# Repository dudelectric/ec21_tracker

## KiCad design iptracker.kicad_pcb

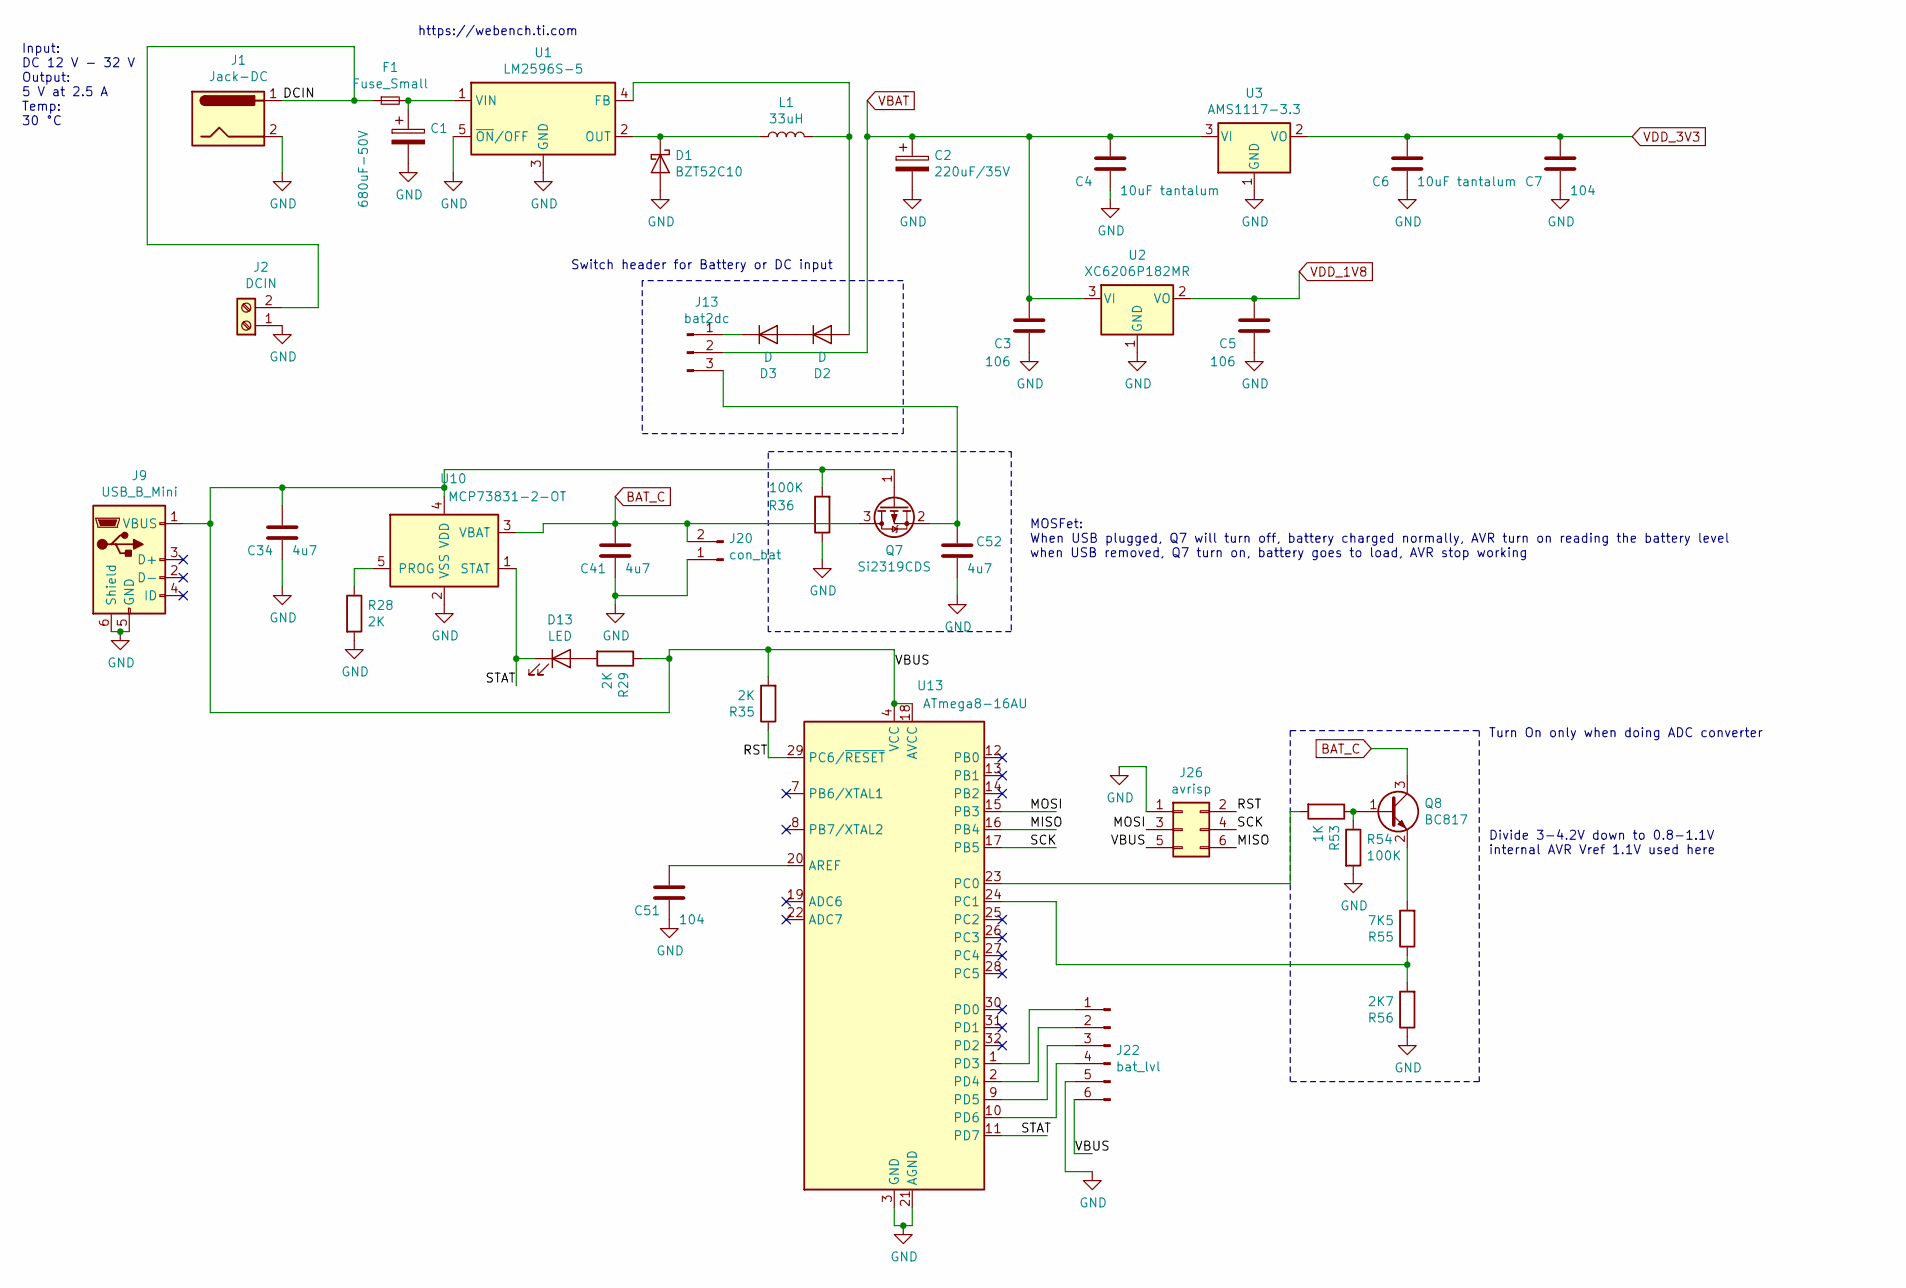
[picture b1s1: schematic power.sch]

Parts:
C1: 680uF-50V; CP_Elec_10x10
C2: 220uF/35V; CP_Elec_10x10
C3, C5: 106; C_0805_2012Metric_Pad1.15x1.40mm_HandSolder
C4, C6: 10uF tantalum; C_1210_3225Metric_Pad1.42x2.65mm_HandSolder
C7, C51: 104; C_0805_2012Metric_Pad1.15x1.40mm_HandSolder
C34, C41, C52: 4u7; C_0805_2012Metric_Pad1.15x1.40mm_HandSolder
D1: BZT52C10; D_SMA_Handsoldering
D2, D3: D; D_SMA_Handsoldering
D13: LED; LED_0805_2012Metric_Pad1.15x1.40mm_HandSolder
F1: Fuse_Small; Fuse_1806_4516Metric
J1: Jack-DC; BarrelJack_Horizontal
J2: DCIN; TerminalBlock_bornier-2_P5.08mm
J9: USB_B_Mini; USB_Mini-B_Lumberg_2486_01_Horizontal
J13: bat2dc; PinHeader_1x03_P2.54mm_Vertical
J20: con_bat; JST_PH_B2B-PH-K_1x02_P2.00mm_Vertical
J22: bat_lvl; PinHeader_1x06_P2.54mm_Vertical
J26: avrisp; PinHeader_2x03_P2.54mm_Vertical
L1: 33uH; L_Neosid_SM-NE127_HandSoldering
Q7: Si2319CDS; SOT-23
Q8: BC817; SOT-23
R28, R29, R35: 2K; R_0805_2012Metric_Pad1.15x1.40mm_HandSolder
R36, R54: 100K; R_0805_2012Metric_Pad1.15x1.40mm_HandSolder
R53: 1K; R_0805_2012Metric_Pad1.15x1.40mm_HandSolder
R55: 7K5; R_0805_2012Metric_Pad1.15x1.40mm_HandSolder
R56: 2K7; R_0805_2012Metric_Pad1.15x1.40mm_HandSolder
U1: LM2596S-5; TO-263-5_TabPin3
U2: XC6206P182MR; SOT-23
U3: AMS1117-3.3; SOT-223-3_TabPin2
U10: MCP73831-2-OT; SOT-23-5
U13: ATmega8-16AU; TQFP-32_7x7mm_P0.8mm

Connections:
/power/DCIN: F1.1, J1.1, J2.2
/power/MISO: J26.6, U13.16 (PB4)
/power/MOSI: J26.3, U13.15 (PB3)
/power/RST: J26.2, R35.1, U13.29 (PC6/~RESET)
/power/SCK: J26.4, U13.17 (PB5)
/power/STAT: D13.1 (K), U10.1 (STAT), U13.11 (PD7)
/power/VBUS: C34.1, J9.1 (VBUS), J22.6, J26.5, Q7.1 (G), R29.1, R35.2, R36.2, U10.4 (VDD), U13.4 (VCC), U13.6 (VCC), U13.18 (AVCC)
BAT_C: C41.1, J20.2, Q7.3 (D), Q8.3 (C), U10.3 (VBAT); also elsewhere on the board
GND: C1.2, C2.2, C3.2, C4.2, C5.2, C6.2, C7.2, C34.2, C41.2, C51.2, C52.2, D1.2 (A), J1.2, J2.1, J9.5 (GND), J9.6 (Shield), J20.1, J22.5, J26.1, R28.2, R36.1, R54.2, R56.1, U1.3 (GND), U1.5 (~ON~/OFF), U2.1 (GND), U3.1 (GND), U10.2 (VSS), U13.3 (GND), U13.5 (GND), U13.21 (AGND); also elsewhere on the board
unnamed: C1.1, F1.2, U1.1 (VIN)
unnamed: C51.1, U13.20 (AREF)
unnamed: C52.1, J13.3, Q7.2 (S)
unnamed: D1.1 (K), L1.1, U1.2 (OUT)
unnamed: D2.1 (K), D3.2 (A)
unnamed: D2.2 (A), L1.2, U1.4 (FB)
unnamed: D3.1 (K), J13.1
unnamed: D13.2 (A), R29.2
unnamed: J22.1, U13.1 (PD3)
unnamed: J22.2, U13.2 (PD4)
unnamed: J22.3, U13.9 (PD5)
unnamed: J22.4, U13.10 (PD6)
unnamed: Q8.1 (B), R53.1, R54.1
unnamed: Q8.2 (E), R55.2
unnamed: R28.1, U10.5 (PROG)
unnamed: R53.2, U13.23 (PC0)
unnamed: R55.1, R56.2, U13.24 (PC1)
VBAT: C2.1, C3.1, C4.1, J13.2, U2.3 (VI), U3.3 (VI); also elsewhere on the board
VDD_1V8: C5.1, U2.2 (VO)
VDD_3V3: C6.1, C7.1, U3.2 (VO); also elsewhere on the board

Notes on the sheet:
Input: DC 12 V - 32 V Output: 5 V at 2.5 A Temp: 30 °C
https://webench.ti.com
Switch header for Battery or DC input
Turn On only when doing ADC converter
Divide 3-4.2V down to 0.8-1.1V internal AVR Vref 1.1V used here
MOSFet: When USB plugged, Q7 will turn off, battery charged normally, AVR turn on reading the battery level when USB removed, Q7 turn on, battery goes to load, AVR stop working

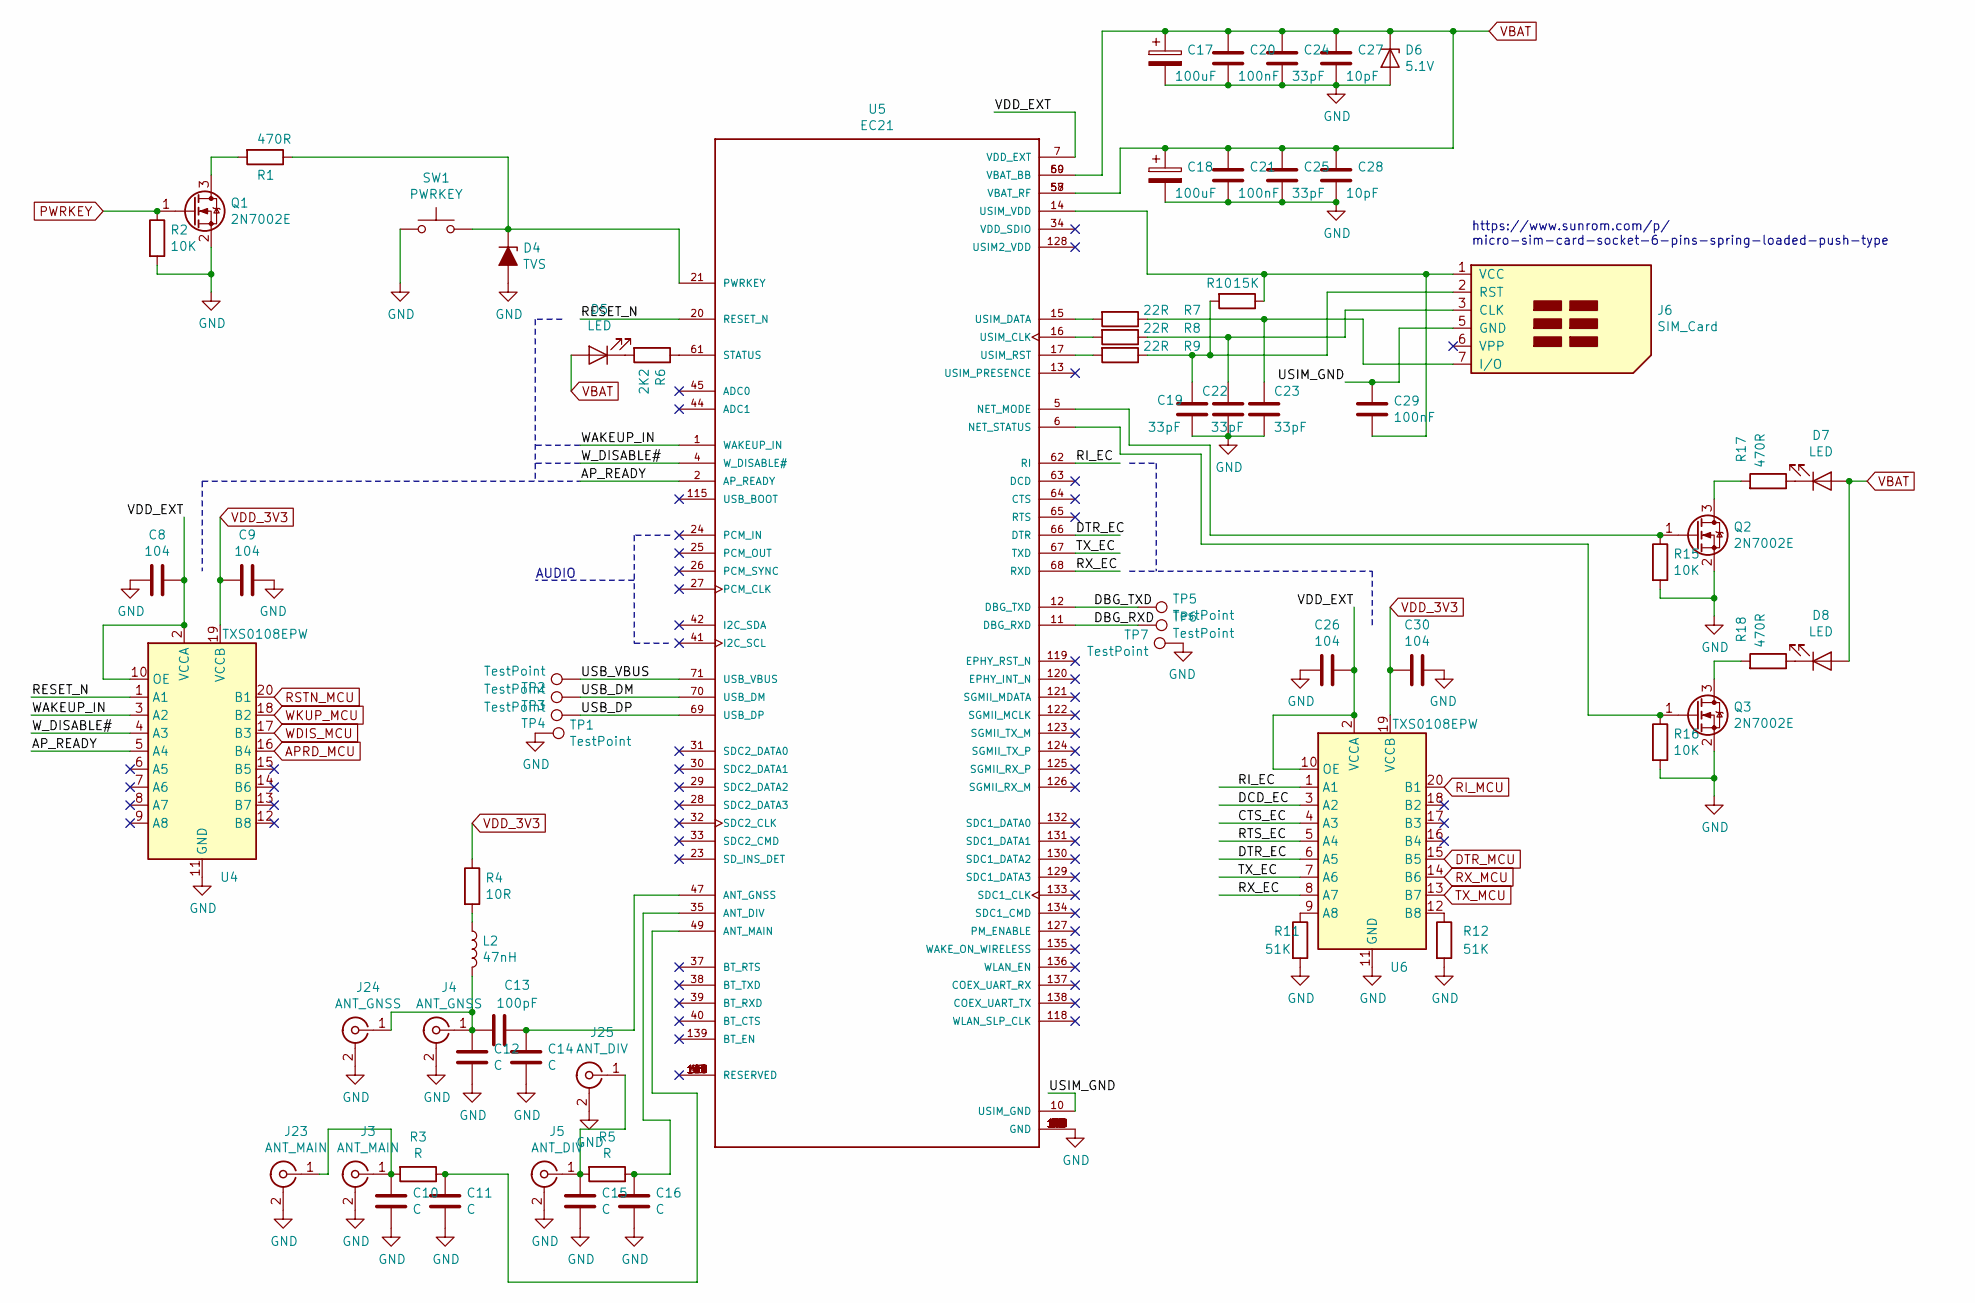
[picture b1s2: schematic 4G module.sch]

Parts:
C8, C9, C26, C30: 104; C_0805_2012Metric_Pad1.15x1.40mm_HandSolder
C10, C11, C12, C14, C15, C16: C; C_0805_2012Metric_Pad1.15x1.40mm_HandSolder
C13: 100pF; C_0805_2012Metric_Pad1.15x1.40mm_HandSolder
C17, C18: 100uF; CP_Elec_6.3x5.4
C19, C22, C23, C24, C25: 33pF; C_0805_2012Metric_Pad1.15x1.40mm_HandSolder
C20, C21, C29: 100nF; C_0805_2012Metric_Pad1.15x1.40mm_HandSolder
C27, C28: 10pF; C_0805_2012Metric_Pad1.15x1.40mm_HandSolder
D4: TVS; D_SMA_Handsoldering
D5, D7, D8: LED; LED_0805_2012Metric_Pad1.15x1.40mm_HandSolder
D6: 5.1V; D_SMA_Handsoldering
J3: ANT_MAIN; U.FL_Hirose_U.FL-R-SMT-1_Vertical
J4: ANT_GNSS; U.FL_Hirose_U.FL-R-SMT-1_Vertical
J5: ANT_DIV; U.FL_Hirose_U.FL-R-SMT-1_Vertical
J6: SIM_Card; Micro SIM Card Socket - 6 pins - Spring Loaded Push type
J23: ANT_MAIN; SMA_Molex_73251-2200_Horizontal
J24: ANT_GNSS; SMA_Molex_73251-2200_Horizontal
J25: ANT_DIV; SMA_Molex_73251-2200_Horizontal
L2: 47nH; L_0805_2012Metric_Pad1.15x1.40mm_HandSolder
Q1, Q2, Q3: 2N7002E; SOT-23
R1, R17, R18: 470R; R_0805_2012Metric_Pad1.15x1.40mm_HandSolder
R2, R15, R16: 10K; R_0805_2012Metric_Pad1.15x1.40mm_HandSolder
R3, R5: R; R_0805_2012Metric_Pad1.15x1.40mm_HandSolder
R4: 10R; R_0805_2012Metric_Pad1.15x1.40mm_HandSolder
R6: 2K2; R_0805_2012Metric_Pad1.15x1.40mm_HandSolder
R7, R8, R9: 22R; R_0805_2012Metric_Pad1.15x1.40mm_HandSolder
R10: 15K; R_0805_2012Metric_Pad1.15x1.40mm_HandSolder
R11, R12: 51K; R_0805_2012Metric_Pad1.15x1.40mm_HandSolder
SW1: PWRKEY; SW_PUSH_6mm
TP1, TP2, TP3, TP4, TP5, TP6, TP7: TestPoint; TestPoint_Pad_1.5x1.5mm
U4, U6: TXS0108EPW; TSSOP-20_4.4x6.5mm_P0.65mm
U5: EC21; XDCR_EC21

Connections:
/4G module/AP_READY: U4.5 (A4), U5.2 (AP_READY)
/4G module/DBG_RXD: TP6.1, U5.11 (DBG_RXD)
/4G module/DBG_TXD: TP5.1, U5.12 (DBG_TXD)
/4G module/DTR_EC: U5.66 (DTR), U6.6 (A5)
/4G module/RESET_N: U4.1 (A1), U5.20 (RESET_N)
/4G module/RI_EC: U5.62 (RI), U6.1 (A1)
/4G module/RX_EC: U5.68 (RXD), U6.8 (A7)
/4G module/TX_EC: U5.67 (TXD), U6.7 (A6)
/4G module/USB_DM: TP3.1, U5.70 (USB_DM)
/4G module/USB_DP: TP4.1, U5.69 (USB_DP)
/4G module/USB_VBUS: TP2.1, U5.71 (USB_VBUS)
/4G module/USIM_GND: C29.1, J6.5 (GND), U5.10 (USIM_GND)
/4G module/VDD_EXT: C8.1, C26.1, U4.2 (VCCA), U4.10 (OE), U5.7 (VDD_EXT), U6.2 (VCCA), U6.10 (OE)
/4G module/WAKEUP_IN: U4.3 (A2), U5.1 (WAKEUP_IN)
/4G module/W_DISABLE#: U4.4 (A3), U5.4 (W_DISABLE#)
APRD_MCU: U4.16 (B4); also elsewhere on the board
DTR_MCU: U6.15 (B5); also elsewhere on the board
GND: C8.2, C9.2, C10.2, C11.2, C12.2, C14.2, C15.2, C16.2, C17.2, C18.2, C19.2, C20.2, C21.2, C22.2, C23.2, C24.2, C25.2, C26.2, C27.2, C28.2, C30.2, D4.2 (A), D6.2 (A), J3.2 (Ext), J4.2 (Ext), J5.2 (Ext), J23.2 (Ext), J24.2 (Ext), J25.2 (Ext), Q1.2 (S), Q2.2 (S), Q3.2 (S), R2.2, R11.2, R12.2, R15.2, R16.2, SW1.1, TP1.1, TP7.1, U4.11 (GND), U5.8 (GND), U5.9 (GND), U5.19 (GND), U5.22 (GND), U5.36 (GND), U5.46 (GND), U5.48 (GND), U5.50 (GND), U5.51 (GND), U5.52 (GND), U5.53 (GND), U5.54 (GND), U5.56 (GND), U5.72 (GND), U5.85 (GND), U5.86 (GND), U5.87 (GND), U5.88 (GND), U5.89 (GND), U5.90 (GND), U5.91 (GND), U5.92 (GND), U5.93 (GND), U5.94 (GND), U5.95 (GND), U5.96 (GND), U5.97 (GND), U5.98 (GND), U5.99 (GND), U5.100 (GND), U5.101 (GND), U5.102 (GND), U5.103 (GND), U5.104 (GND), U5.105 (GND), U5.106 (GND), U5.107 (GND), U5.108 (GND), U5.109 (GND), U5.110 (GND), U5.111 (GND), U5.112 (GND), U6.11 (GND); also elsewhere on the board
unnamed: C10.1, J3.1 (In), J23.1 (In), R3.2
unnamed: C11.1, R3.1, U5.49 (ANT_MAIN)
unnamed: C12.1, C13.2, J4.1 (In), J24.1 (In), L2.2
unnamed: C13.1, C14.1, U5.47 (ANT_GNSS)
unnamed: C15.1, J5.1 (In), J25.1 (In), R5.2
unnamed: C16.1, R5.1, U5.35 (ANT_DIV)
unnamed: C19.1, J6.2 (RST), R9.1, R10.2
unnamed: C22.1, J6.3 (CLK), R8.1
unnamed: C23.1, J6.7 (I/O), R7.1
unnamed: C29.2, J6.1 (VCC), R10.1, U5.14 (USIM_VDD)
unnamed: D4.1 (K), R1.1, SW1.2, U5.21 (PWRKEY)
unnamed: D5.1 (K), R6.2
unnamed: D7.1 (K), R17.1
unnamed: D8.1 (K), R18.1
unnamed: L2.1, R4.2
unnamed: Q1.3 (D), R1.2
unnamed: Q2.1 (G), R15.1, U5.5 (NET_MODE)
unnamed: Q2.3 (D), R17.2
unnamed: Q3.1 (G), R16.1, U5.6 (NET_STATUS)
unnamed: Q3.3 (D), R18.2
unnamed: R6.1, U5.61 (STATUS)
unnamed: R7.2, U5.15 (USIM_DATA)
unnamed: R8.2, U5.16 (USIM_CLK)
unnamed: R9.2, U5.17 (USIM_RST)
unnamed: R11.1, U6.9 (A8)
unnamed: R12.1, U6.12 (B8)
unnamed: U5.3 (RESERVED), U5.18 (RESERVED), U5.43 (RESERVED), U5.55 (RESERVED), U5.113 (RESERVED), U5.114 (RESERVED), U5.116 (RESERVED), U5.117 (RESERVED), U5.140 (RESERVED), U5.141 (RESERVED), U5.142 (RESERVED), U5.143 (RESERVED), U5.144 (RESERVED)
PWRKEY: Q1.1 (G), R2.1
RI_MCU: U6.20 (B1); also elsewhere on the board
RSTN_MCU: U4.20 (B1); also elsewhere on the board
RX_MCU: U6.14 (B6); also elsewhere on the board
TX_MCU: U6.13 (B7); also elsewhere on the board
VBAT: C17.1, C18.1, C20.1, C21.1, C24.1, C25.1, C27.1, C28.1, D5.2 (A), D6.1 (K), D7.2 (A), D8.2 (A), U5.57 (VBAT_RF), U5.58 (VBAT_RF), U5.59 (VBAT_BB), U5.60 (VBAT_BB); also elsewhere on the board
VDD_3V3: C9.1, C30.1, R4.1, U4.19 (VCCB), U6.19 (VCCB); also elsewhere on the board
WDIS_MCU: U4.17 (B3); also elsewhere on the board
WKUP_MCU: U4.18 (B2); also elsewhere on the board

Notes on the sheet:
AUDIO
https://www.sunrom.com/p/ micro-sim-card-socket-6-pins-spring-loaded-push-type

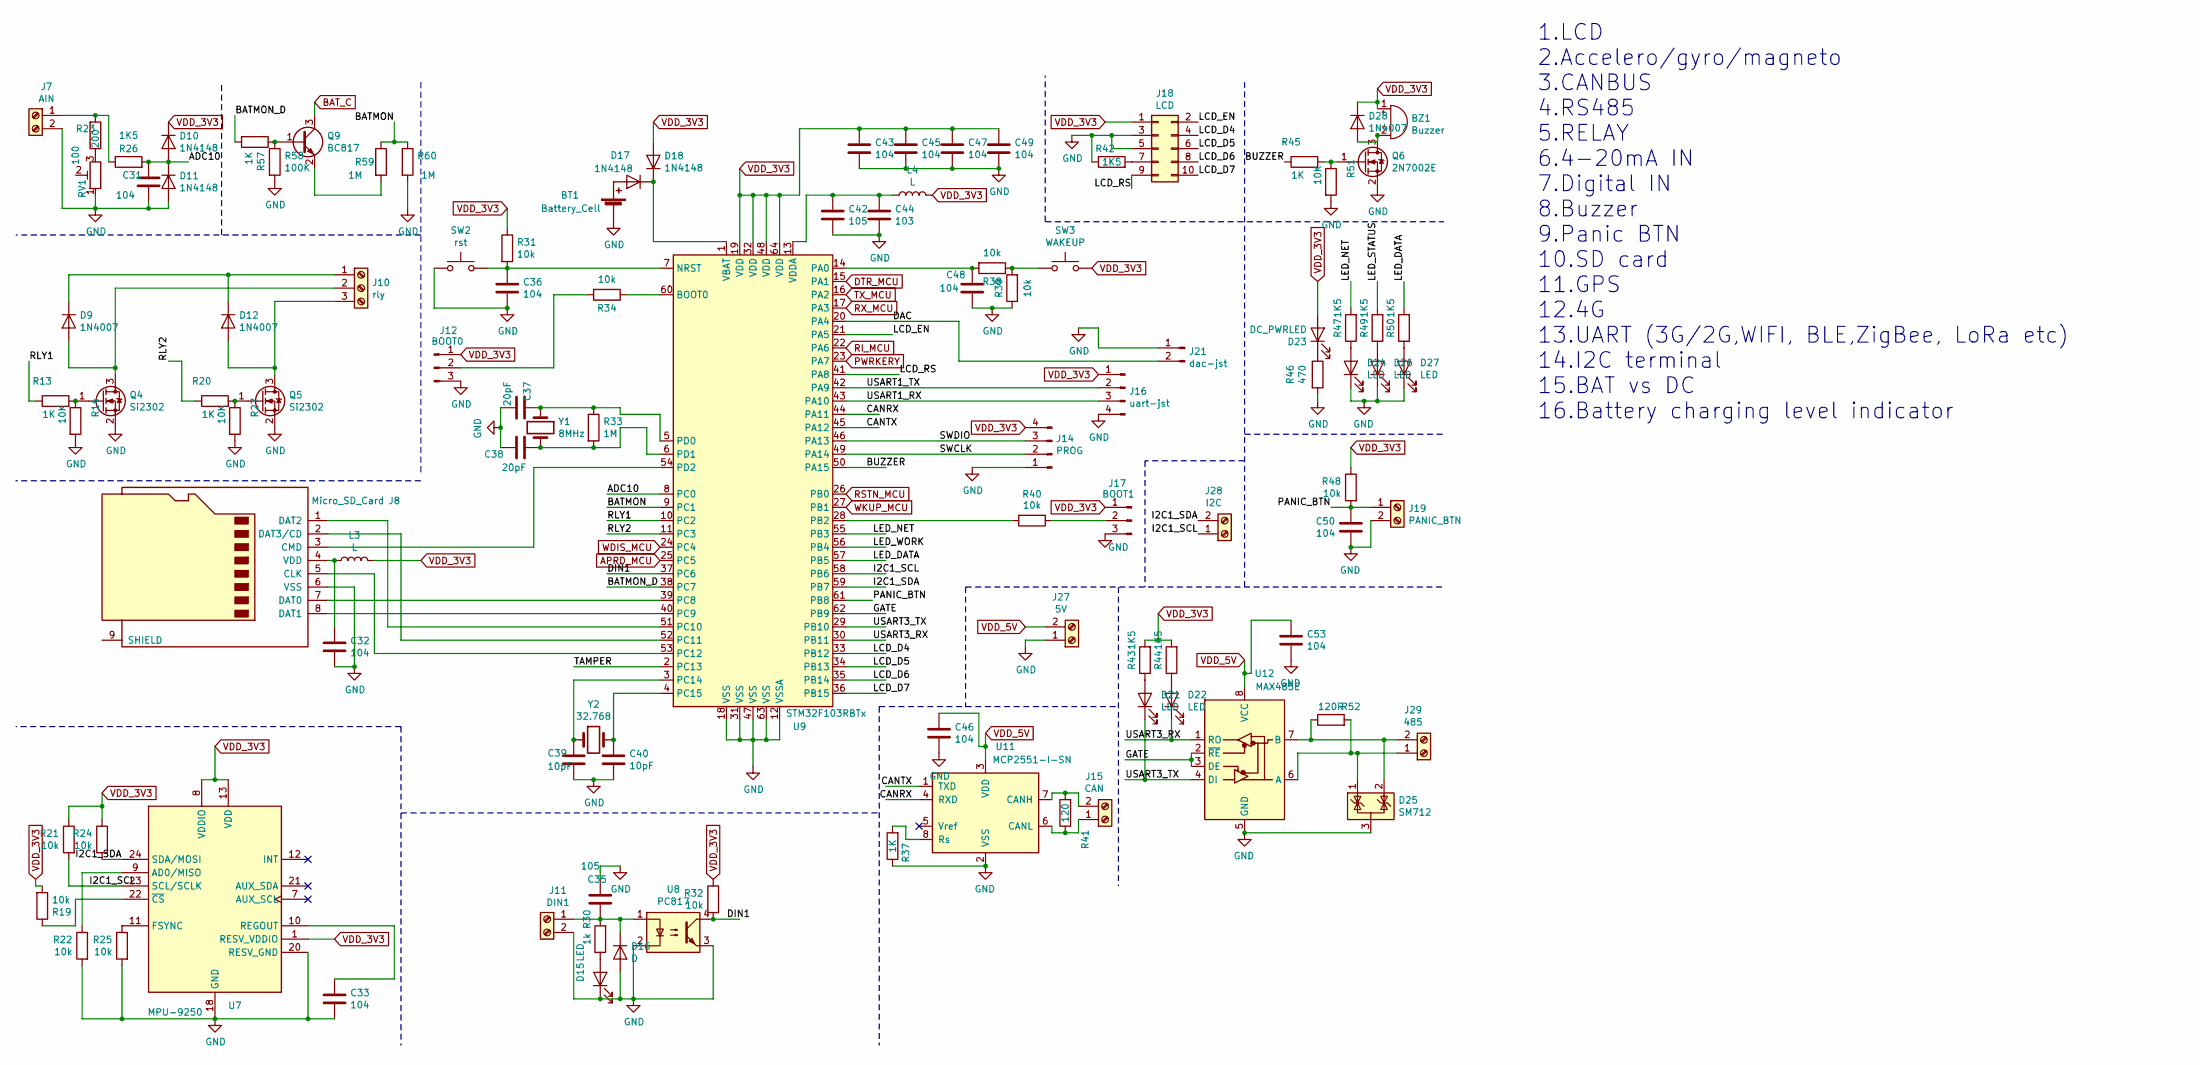
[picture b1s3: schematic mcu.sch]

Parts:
BT1: Battery_Cell; BatteryHolder_Keystone_3001_1x12mm
BZ1: Buzzer; Buzzer_12x9.5RM7.6
C31, C32, C33, C36, C43, C45, C46, C47, C48, C49, C50, C53: 104; C_0805_2012Metric_Pad1.15x1.40mm_HandSolder
C35, C42: 105; C_0805_2012Metric_Pad1.15x1.40mm_HandSolder
C37, C38: 20pF; C_0805_2012Metric_Pad1.15x1.40mm_HandSolder
C39, C40: 10pF; C_0805_2012Metric_Pad1.15x1.40mm_HandSolder
C44: 103; C_0805_2012Metric_Pad1.15x1.40mm_HandSolder
D9, D12, D28: 1N4007; D_SMA_Handsoldering
D10, D11, D17, D18: 1N4148; D_MELF
D15, D21, D22, D24, D26, D27: LED; LED_0805_2012Metric_Pad1.15x1.40mm_HandSolder
D16: D; D_MELF
D23: DC_PWRLED; LED_0805_2012Metric_Pad1.15x1.40mm_HandSolder
D25: SM712; SOT-23
J7: AIN; TerminalBlock_bornier-2_P5.08mm
J8: Micro_SD_Card; GCT-MEM2055-00-190-01-A
J10: rly; TerminalBlock_bornier-3_P5.08mm
J11: DIN1; TerminalBlock_bornier-2_P5.08mm
J12: BOOT0; PinHeader_1x03_P2.54mm_Vertical
J14: PROG; PinHeader_1x04_P2.54mm_Vertical
J15: CAN; TerminalBlock_bornier-2_P5.08mm
J16: uart-jst; JST_PH_B4B-PH-K_1x04_P2.00mm_Vertical
J17: BOOT1; PinHeader_1x03_P2.54mm_Vertical
J18: LCD; JST_PHD_B10B-PHDSS_2x05_P2.00mm_Vertical
J19: PANIC_BTN; TerminalBlock_bornier-2_P5.08mm
J21: dac-jst; JST_PH_B2B-PH-K_1x02_P2.00mm_Vertical
J27: 5V; TerminalBlock_bornier-2_P5.08mm
J28: I2C; TerminalBlock_bornier-2_P5.08mm
J29: 485; TerminalBlock_bornier-2_P5.08mm
L3, L4: L; L_0805_2012Metric_Pad1.15x1.40mm_HandSolder
Q4, Q5: Si2302; SOT-23
Q6: 2N7002E; SOT-23
Q9: BC817; SOT-23
R13, R20, R37, R45, R57: 1K; R_0805_2012Metric_Pad1.15x1.40mm_HandSolder
R14, R27, R51: 10K; R_0805_2012Metric_Pad1.15x1.40mm_HandSolder
R19, R21, R22, R24, R25, R31, R32, R34, R38, R39, R40, R48: 10k; R_0805_2012Metric_Pad1.15x1.40mm_HandSolder
R23: 200; R_0805_2012Metric_Pad1.15x1.40mm_HandSolder
R26, R42, R43, R44, R47, R49, R50: 1K5; R_0805_2012Metric_Pad1.15x1.40mm_HandSolder
R30: 1k; R_0805_2012Metric_Pad1.15x1.40mm_HandSolder
R33, R59, R60: 1M; R_0805_2012Metric_Pad1.15x1.40mm_HandSolder
R41: 120; R_0805_2012Metric_Pad1.15x1.40mm_HandSolder
R46: 470; R_0805_2012Metric_Pad1.15x1.40mm_HandSolder
R52: 120R; R_0805_2012Metric_Pad1.15x1.40mm_HandSolder
R58: 100K; R_0805_2012Metric_Pad1.15x1.40mm_HandSolder
RV1: 100; Potentiometer_Vishay_TS53YL_Vertical
SW2: rst; SW_PUSH_6mm
SW3: WAKEUP; SW_PUSH_6mm
U7: MPU-9250; InvenSense_QFN-24_3x3mm_P0.4mm
U8: PC817; DIP-4_W7.62mm
U9: STM32F103RBTx; LQFP-64_10x10mm_P0.5mm
U11: MCP2551-I-SN; SOIC-8_3.9x4.9mm_P1.27mm
U12: MAX485E; SOIC-8_3.9x4.9mm_P1.27mm
Y1: 8MHz; Crystal_HC49-4H_Vertical
Y2: 32.768; Crystal_SMD_SeikoEpson_MA406-4Pin_11.7x4.0mm_HandSoldering

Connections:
/mcu/ADC10: C31.1, D10.2 (A), D11.1 (K), R26.2, U9.8 (PC0)
/mcu/BATMON: R59.1, R60.1, U9.9 (PC1)
/mcu/BATMON_D: R57.2, U9.38 (PC7)
/mcu/BUZZER: R45.1, U9.50 (PA15)
/mcu/CANRX: U9.44 (PA11), U11.4 (RXD)
/mcu/CANTX: U9.45 (PA12), U11.1 (TXD)
/mcu/DAC: J21.2, U9.20 (PA4)
/mcu/DIN1: R32.2, U8.4, U9.37 (PC6)
/mcu/GATE: U9.62 (PB9), U12.2 (~RE), U12.3 (DE)
/mcu/I2C1_SCL: J28.1, R21.2, U7.23 (SCL/SCLK), U9.58 (PB6)
/mcu/I2C1_SDA: J28.2, R24.2, U7.24 (SDA/MOSI), U9.59 (PB7)
/mcu/LCD_D4: J18.4, U9.33 (PB12)
/mcu/LCD_D5: J18.6, U9.34 (PB13)
/mcu/LCD_D6: J18.8, U9.35 (PB14)
/mcu/LCD_D7: J18.10, U9.36 (PB15)
/mcu/LCD_EN: J18.2, U9.21 (PA5)
/mcu/LCD_RS: J18.9, U9.41 (PA8)
/mcu/LED_DATA: R50.2, U9.57 (PB5)
/mcu/LED_NET: R47.2, U9.55 (PB3)
/mcu/PANIC_BTN: C50.1, J19.1, R48.2, U9.61 (PB8)
/mcu/RLY1: R13.1, U9.10 (PC2)
/mcu/RLY2: R20.1, U9.11 (PC3)
/mcu/SWCLK: J14.2, U9.49 (PA14)
/mcu/SWDIO: J14.3, U9.46 (PA13)
/mcu/USART1_RX: J16.3, U9.43 (PA10)
/mcu/USART1_TX: J16.2, U9.42 (PA9)
/mcu/USART3_RX: D22.1 (K), U9.30 (PB11), U12.1 (RO)
/mcu/USART3_TX: D21.1 (K), U9.29 (PB10), U12.4 (DI)
APRD_MCU: U9.25 (PC5); also elsewhere on the board
BAT_C: Q9.3 (C); also elsewhere on the board
DTR_MCU: U9.15 (PA1); also elsewhere on the board
GND: BT1.2 (-), C31.2, C32.2, C33.2, C35.1, C36.2, C37.1, C38.2, C39.1, C40.2, C42.2, C43.2, C44.2, C45.2, C46.2, C47.2, C48.2, C49.2, C50.2, C53.2, D11.2 (A), D15.1 (K), D16.2 (A), D24.1 (K), D25.3 (A), D26.1 (K), D27.1 (K), J7.2, J8.6 (VSS), J11.2, J12.3, J14.1, J16.4, J17.3, J18.3, J18.5, J19.2, J21.1, J27.1, Q4.2 (S), Q5.2 (S), Q6.2 (S), R14.2, R22.2, R25.2, R27.2, R37.1, R39.1, R42.1, R46.2, R51.2, R58.2, R60.2, RV1.1, SW2.1, U7.18 (GND), U7.20 (RESV_GND), U8.2, U8.3, U9.12 (VSSA), U9.18 (VSS), U9.31 (VSS), U9.47 (VSS), U9.63 (VSS), U11.2 (VSS), U12.5 (GND); also elsewhere on the board
unnamed: BT1.1 (+), D17.2 (A)
unnamed: BZ1.2 (+), D28.2 (A), Q6.3 (D)
unnamed: C32.1, J8.4 (VDD), L3.1
unnamed: C33.1, U7.10 (REGOUT)
unnamed: C35.2, D16.1 (K), J11.1, R30.2, U8.1
unnamed: C36.1, R31.2, SW2.2, U9.7 (NRST)
unnamed: C37.2, R33.1, U9.5 (PD0), Y1.1
unnamed: C38.1, R33.2, U9.6 (PD1), Y1.2
unnamed: C39.2, U9.3 (PC14), Y2.1
unnamed: C40.1, U9.4 (PC15), Y2.2
unnamed: C42.1, C44.1, L4.1, U9.13 (VDDA)
unnamed: C48.1, R38.2, U9.14 (PA0)
unnamed: D9.2 (A), J10.2, Q4.3 (D)
unnamed: D9.1 (K), D12.1 (K), J10.1
unnamed: D12.2 (A), J10.3, Q5.3 (D)
unnamed: D15.2 (A), R30.1
unnamed: D17.1 (K), D18.1 (K), U9.1 (VBAT)
unnamed: D21.2 (A), R43.1
unnamed: D22.2 (A), R44.1
unnamed: D23.1 (K), R46.1
unnamed: D24.2 (A), R47.1
unnamed: D25.1 (K), J29.1, R52.2, U12.6 (A)
unnamed: D25.2 (K), J29.2, R52.1, U12.7 (B)
unnamed: D26.2 (A), R49.1
unnamed: D27.2 (A), R50.1
unnamed: J7.1, R23.2, R26.1
unnamed: J8.1 (DAT2), U9.51 (PC10)
unnamed: J8.2 (DAT3/CD), U9.52 (PC11)
unnamed: J8.3 (CMD), U9.54 (PD2)
unnamed: J8.5 (CLK), U9.53 (PC12)
unnamed: J8.7 (DAT0), U9.39 (PC8)
unnamed: J8.8 (DAT1), U9.40 (PC9)
unnamed: J12.2, R34.2
unnamed: J15.1, R41.1, U11.6 (CANL)
unnamed: J15.2, R41.2, U11.7 (CANH)
unnamed: J17.2, R40.1
unnamed: J18.7, R42.2
unnamed: Q4.1 (G), R13.2, R14.1
unnamed: Q5.1 (G), R20.2, R27.1
unnamed: Q6.1 (G), R45.2, R51.1
unnamed: Q9.1 (B), R57.1, R58.1
unnamed: Q9.2 (E), R59.2
unnamed: R19.1, U7.22 (~CS)
unnamed: R22.1, U7.9 (AD0/MISO)
unnamed: R23.1, RV1.3
unnamed: R25.1, U7.11 (FSYNC)
unnamed: R34.1, U9.60 (BOOT0)
unnamed: R37.2, U11.8 (Rs)
unnamed: R38.1, R39.2, SW3.1
unnamed: R40.2, U9.28 (PB2)
RI_MCU: U9.22 (PA6); also elsewhere on the board
RSTN_MCU: U9.26 (PB0); also elsewhere on the board
RX_MCU: U9.17 (PA3); also elsewhere on the board
TX_MCU: U9.16 (PA2); also elsewhere on the board
VDD_3V3: BZ1.1 (-), C43.1, C45.1, C47.1, C49.1, D10.1 (K), D18.2 (A), D23.2 (A), D28.1 (K), J12.1, J14.4, J16.1, J17.1, J18.1, L3.2, L4.2, R19.2, R21.1, R24.1, R31.1, R32.1, R43.2, R44.2, R48.1, SW3.2, U7.1 (RESV_VDDIO), U7.8 (VDDIO), U7.13 (VDD), U9.19 (VDD), U9.32 (VDD), U9.48 (VDD), U9.64 (VDD); also elsewhere on the board
VDD_5V: C46.1, C53.1, J27.2, U11.3 (VDD), U12.8 (VCC)
WDIS_MCU: U9.24 (PC4); also elsewhere on the board
WKUP_MCU: U9.27 (PB1); also elsewhere on the board

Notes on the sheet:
1.LCD 2.Accelero/gyro/magneto 3.CANBUS 4.RS485 5.RELAY 6.4-20mA IN 7.Digital IN 8.Buzzer 9.Panic BTN 10.SD card 11.GPS 12.4G 13.UART (3G/2G,WIFI, BLE,ZigBee, LoRa etc) 14.I2C terminal 15.BAT vs DC 16.Battery charging level indicator

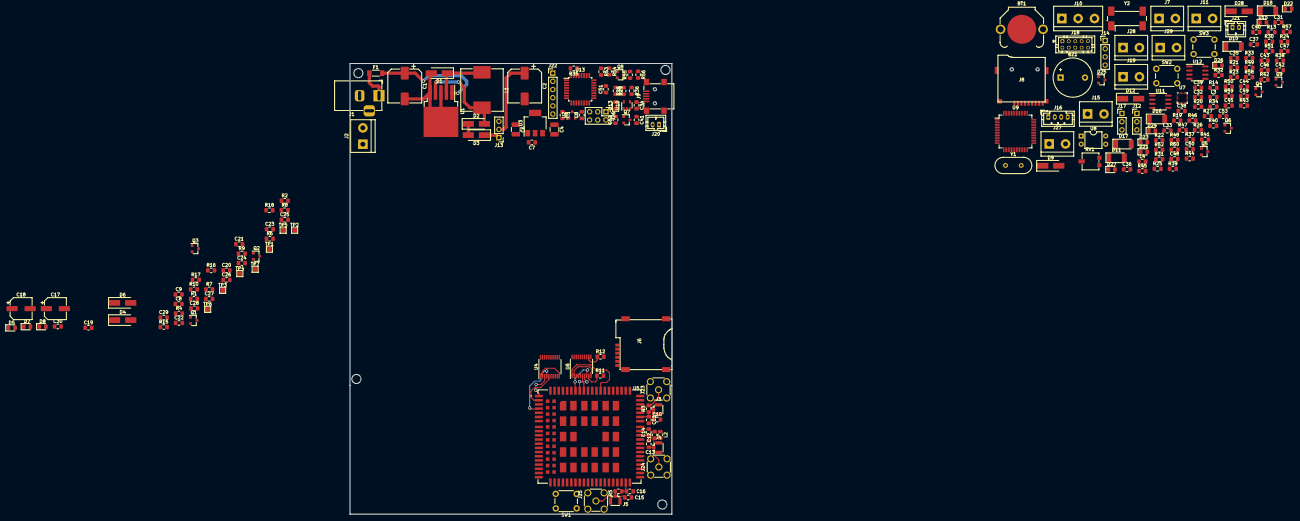
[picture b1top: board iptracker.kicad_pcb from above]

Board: 2 copper layers, 100.0 x 140.0 mm, 209 parts (0 on the bottom side), 159 nets.

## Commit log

2020-11-25 init
2020-11-25 pdf sch
